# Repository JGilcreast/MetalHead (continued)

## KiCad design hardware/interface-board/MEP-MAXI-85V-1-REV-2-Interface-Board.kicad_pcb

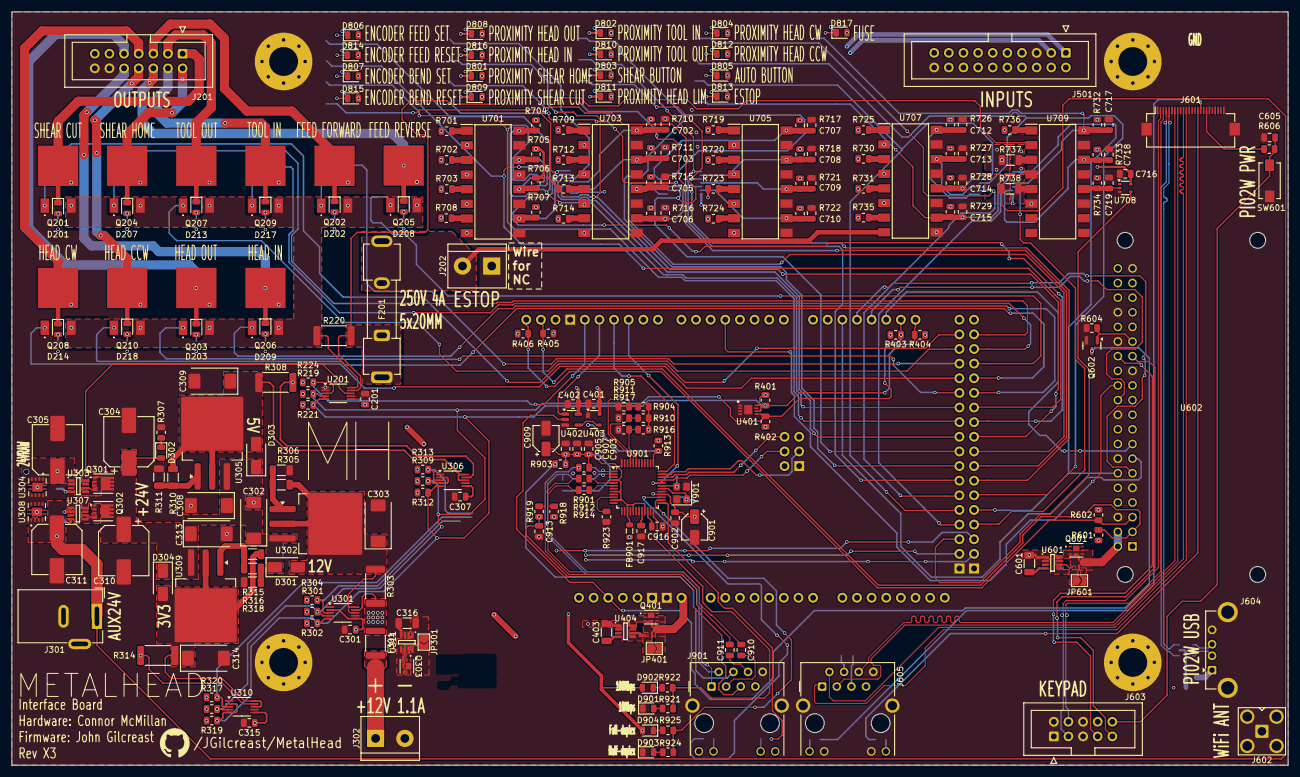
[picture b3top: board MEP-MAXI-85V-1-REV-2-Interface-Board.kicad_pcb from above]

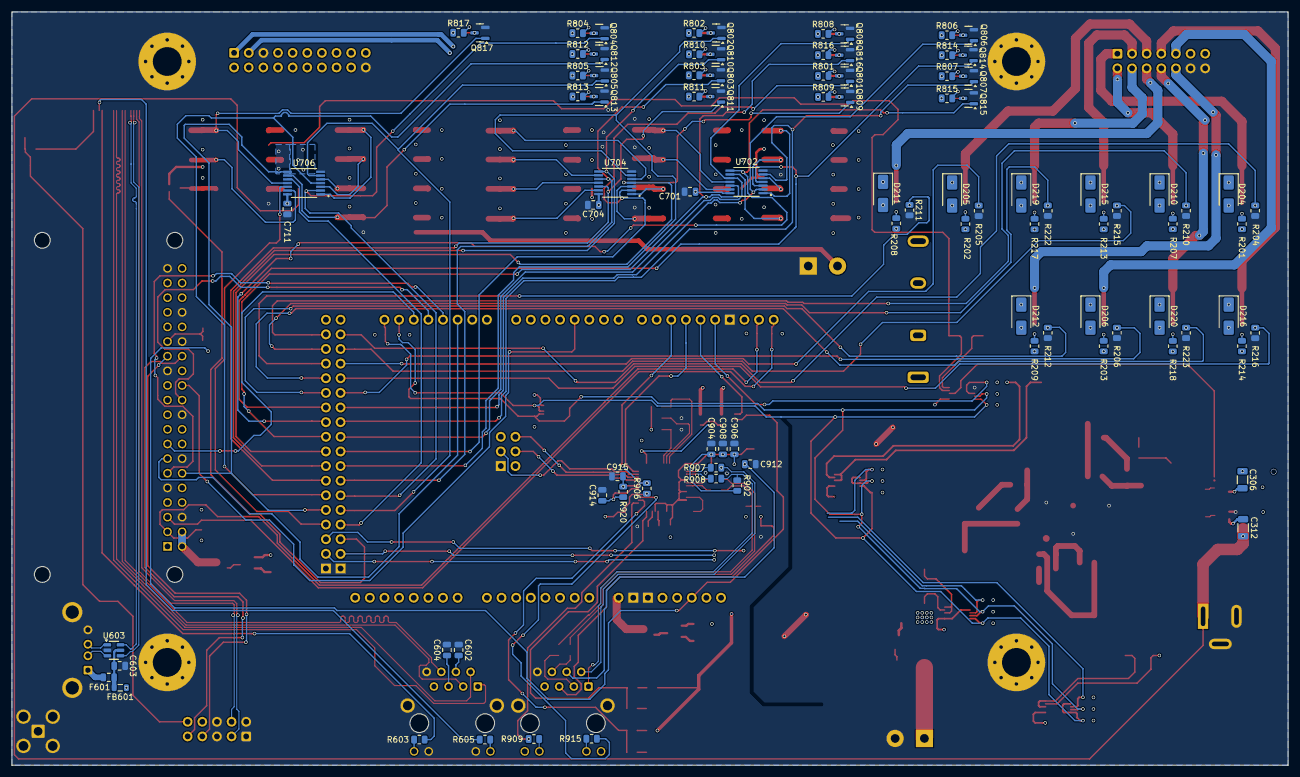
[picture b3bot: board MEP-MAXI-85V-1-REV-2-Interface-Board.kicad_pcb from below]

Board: 4 copper layers, 221.5 x 130.8 mm, 330 parts (93 on the bottom side), 244 nets.

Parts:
A401: Arduino_Due_Shield
C201, C301, C307, C315, C902, C903, C904, C905, C906, C907, C908: 0.1uF; C_0805_2012Metric
C302, C303, C308, C309, C313, C314: 10uF 50V; CP_EIA-7343-31_Kemet-D
C304, C305, C310, C311: 330uF 25V; CP_Elec_8x10.5
C306, C312, C316, C403, C601: 100nF; C_1206_3216Metric
C401, C402, C701, C702, C703, C704, C705, C706, C707, C708, C709, C710, C711, C712, C713, C714, C715, C716, C717, C718, C719: 1uF; C_0805_2012Metric
C602, C603, C604, C605: 100nF; C_0805_2012Metric
C901, C909: 10uF; CP_Elec_4x5.4
C910, C911: 6.8nF; C_0805_2012Metric
C912: 22nF; C_0805_2012Metric
C913, C916: 10nF; C_0805_2012Metric
C914, C915: 18pF; C_0805_2012Metric
C917: 4.7uF; C_0805_2012Metric
D201, D202, D203, D207, D208, D209, D213, D214, D217, D218, D901, D902, D903, D904: RED; LED_0805_2012Metric
D204, D205, D206, D210, D211, D212, D215, D216, D219, D220: SMAJ24A; D_SMA
D301, D303, D304: 1N4002 M2; D_SMA
D302, D801, D802, D803, D804, D805, D806, D807, D808, D809, D810, D811, D812, D813, D814, D815, D816, D817: BLUE; LED_0805_2012Metric
F201: 3512P; Fuseholder_Clip-5x20mm_Keystone_3512P_Inline_P23.62x7.27mm_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
F301: 16V/1.1A; Fuse_1812_4532Metric
F601: 500mA; Fuse_0805_2012Metric
FB601: 330R; L_0805_2012Metric
FB901: 120R; L_0805_2012Metric
H101, H102, H103, H104: MountingHole_Pad; MountingHole_5mm_Pad_Via
J201: Conn_02x07_Odd_Even; IDC-Header_2x07_P2.54mm_Vertical
J202, J302: Screw_Terminal_01x02; TerminalBlock_bornier-2_P5.08mm
J301: Barrel_Jack_MountingPin; BarrelJack_Wuerth_6941xx301002
J501: Conn_02x10_Odd_Even; IDC-Header_2x10_P2.54mm_Vertical
J601: Conn_01x24_MountingPin; Hirose_FH12-24S-0.5SH_1x24-1MP_P0.50mm_Horizontal
J602: Conn_Coaxial; SMA_Amphenol_901-143_Horizontal
J603: Conn_02x05_Odd_Even; IDC-Header_2x05_P2.54mm_Vertical
J604: USB_A; USB_A_Connfly_DS1095
J605, J901: RJ45_Hanrun_HR911105A_Horizontal
JP301, JP401, JP601: SolderJumper_2_Open; SolderJumper-2_P1.3mm_Open_TrianglePad1.0x1.5mm
Q201, Q202, Q203, Q204, Q205, Q206, Q207, Q208, Q209, Q210: IRFR7540TRPBF
Q301, Q302: DMT6007LFG; DMP4013LFG7
Q303, Q401, Q601: SSM6K518NU; SOT-1220UDFN6B_TOS
Q602, Q801, Q802, Q803, Q804, Q805, Q806, Q807, Q808, Q809, Q810, Q811, Q812, Q813, Q814, Q815, Q816, Q817: BSS138 JI; SOT-23
R201, R202, R203, R207, R208, R209, R213, R214, R217, R218, R801, R802, R803, R804, R805, R806, R807, R808, R809, R810, R811, R812, R813, R814, R815, R816, R817: 200R; R_0805_2012Metric
R204, R205, R206, R210, R211, R212, R215, R216, R219, R221, R222, R223, R224, R301, R302, R304, R309, R312, R313, R317, R319, R320, R401, R402, R403, R404, R604, R906, R913: 10K; R_0805_2012Metric
R220, R303, R308, R314: 2mR; R_2512_6332Metric
R305, R310, R315: 300R; R_1206_3216Metric
R306: 2K580; R_1206_3216Metric
R307: 2K2; R_0805_2012Metric
R311: 900R; R_1206_3216Metric
R316: 470R; R_1206_3216Metric
R318: 22R; R_1206_3216Metric
R405, R406, R601, R602: 4K7; R_0805_2012Metric
R603, R605, R606: 510R; R_0805_2012Metric
R701, R702, R703, R708, R709, R712, R713, R714, R719, R720, R723, R724, R725, R730, R731, R735, R736: 105R; R_0805_2012Metric
R704, R705, R706, R707, R710, R711, R715, R716, R717, R718, R721, R722, R726, R727, R728, R729, R732, R733, R734: 100K; R_0805_2012Metric
R737, R738: 1K2; R_1206_3216Metric
R901, R902: 49R9; R_0805_2012Metric
R903: 10R; R_0805_2012Metric
R904, R905, R909, R910, R911, R915, R916, R917: 330R; R_0805_2012Metric
R907, R908, R912, R914: 0R; R_0805_2012Metric
R918, R919: 82R; R_0805_2012Metric
R920: 1M; R_0805_2012Metric
R921, R922, R924, R925: 130R; R_0805_2012Metric
R923: 12.4K 1%; R_0805_2012Metric
SW601: SW_SPST_Omron_B3FS-100xP; SW_SPST_EVQPE1
U201, U301, U306, U310: INA226; VSSOP-10_3x3mm_P0.5mm
U302, U305, U309: LM1084-ADJ; TO-263-3_TabPin2
U303, U307, U311, U404, U601: LM74700QDDFRQ1; SOT65P280X110-8N
U304, U308: TVS2701DRBR; IC_TVS2701DRBR
U401: AT24C256C-MAHL-E; SON50P300X200X60-9L
U402: NC7SZ08M5X; SOT-23-5
U403: APX811-31UG-7; SOT-143
U602: RASPBERRY_PI_ZERO_2_W; MODULE_RASPBERRY_PI_ZERO_2_W
U603: USBLC6-2SC6; SOT-23-6
U701, U703, U705, U707, U709: LTV-846S; LTV846S
U702, U704, U706: SN74HC14PWR; SOP65P640X120-14N
U708: 74LVC1G14GW-Q100,1; SOT-353_SC-70-5
U901: W5500; LQFP-48_7x7mm_P0.5mm
Y901: 25MHz; Crystal_SMD_3225-4Pin_3.2x2.5mm

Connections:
24VRAW: C305.1, C306.1, J201.11, J501.6, Q301.1 (S), R737.1, U303.1 (EN), U303.5 (ANODE), U304.1 (IN), U304.2 (IN), U304.3 (IN), U304.4 (IN)
+3V3: C201.2, C301.2, C307.2, C315.2, C401.2, C402.2, C701.2, C704.2, C711.2, C716.1, C901.1, C902.1, D902.2 (A), D904.2 (A), FB901.1, J901.9, J901.12, R219.2, R221.1, R224.1, R301.2, R302.1, R304.1, R309.2, R312.1, R313.1, R314.2, R317.2, R319.1, R320.1, R401.1, R402.2, R403.2, R404.1, R405.2, R406.1, R601.2, R602.1, R701.1, R702.1, R703.1, R704.1, R705.1, R706.1, R707.1, R708.1, R709.1, R710.1, R711.1, R712.1, R713.1, R714.1, R715.1, R716.1, R717.1, R718.1, R719.1, R720.1, R721.1, R722.1, R723.1, R724.1, R725.1, R726.1, R727.1, R728.1, R729.1, R730.1, R731.1, R732.1, R733.1, R734.1, R735.1, R736.1, R904.2, R906.2, R910.2, R913.2, R916.2, U201.6 (VS), U301.2 (A0), U301.6 (VS), U306.6 (VS), U310.6 (VS), U310.9 (Vin-), U401.8 (VCC), U402.5 (VCC), U403.4 (VCC), U702.14 (VCC), U704.14 (VCC), U706.14 (VCC), U708.5 (VCC), U901.28 (VDD)
+3V3A: C903.1, C904.1, C905.1, C906.1, C907.1, C908.1, C909.1, FB901.2, R901.2, R902.2, R903.2, U901.4 (AVDD), U901.8 (AVDD), U901.11 (AVDD), U901.15 (AVDD), U901.17 (AVDD), U901.21 (AVDD)
+5V: C601.1, JP601.1 (A), Q601.1 (D), R201.1, R202.1, R203.1, R207.1, R208.1, R209.1, R213.1, R214.1, R217.1, R218.1, R308.2, R801.2, R802.2, R803.2, R804.2, R805.2, R806.2, R807.2, R808.2, R809.2, R810.2, R811.2, R812.2, R813.2, R814.2, R815.2, R816.2, R817.2, U306.9 (Vin-), U601.1 (EN), U601.5 (ANODE)
+12V: C316.1, C403.1, JP301.1 (A), JP401.1 (A), Q303.3 (S), Q401.1 (D), R303.2, U301.9 (Vin-), U311.1 (EN), U311.5 (ANODE), U404.1 (EN), U404.5 (ANODE)
+24V: C302.1, C304.1, C308.1, C310.1, C313.1, D301.1 (K), D302.2 (A), D303.1 (K), D304.1 (K), Q301.3 (D), Q302.3 (D), U201.8 (Vbus), U302.3 (VI), U303.8 (CATHODE), U305.3 (VI), U307.8 (CATHODE), U309.3 (VI)
/Arduino Due/D4_CS1/PIN4: A401.D4 (D4_CS1), U602.24 (GPIO8/SPI_~CE0)
/Arduino Due/D10/PIN10: A401.D10 (D10_CS0), R906.1, U901.32 (~SCS)
/Arduino Due/D11/PIN11: A401.D11, U901.36 (~INT)
/Arduino Due/D12/PIN12: A401.D12, U402.1
/Arduino Due/D13/PIN13: A401.D13, R224.2, U201.3 (~Alert)
/Arduino Due/D22/PIN22: A401.D22, Q201.1 (G), R204.2
/Arduino Due/D23/PIN23: A401.D23, Q204.1 (G), R210.2
/Arduino Due/D24/PIN24: A401.D24, Q207.1 (G), R215.2
/Arduino Due/D25/PIN25: A401.D25, Q209.1 (G), R222.2
/Arduino Due/D26/PIN26: A401.D26, Q202.1 (G), R205.2
/Arduino Due/D27/PIN27: A401.D27, Q205.1 (G), R211.2
/Arduino Due/D28/PIN28: A401.D28, Q208.1 (G), R216.2
/Arduino Due/D29/PIN29: A401.D29, Q210.1 (G), R223.2
/Arduino Due/D30/PIN30: A401.D30, Q203.1 (G), R206.2
/Arduino Due/D31/PIN31: A401.D31, Q206.1 (G), R212.2
/Arduino Due/D32/PIN32: A401.D32, Q806.1 (G), U702.2 (1Y)
/Arduino Due/D33/PIN33: A401.D33, Q814.1 (G), U702.4 (2Y)
/Arduino Due/D34/PIN34: A401.D34, Q807.1 (G), U702.6 (3Y)
/Arduino Due/D35/PIN35: A401.D35, Q815.1 (G), U702.8 (4Y)
/Arduino Due/D36/PIN36: A401.D36, Q808.1 (G), U702.10 (5Y)
/Arduino Due/D37/PIN37: A401.D37, Q816.1 (G), U702.12 (6Y)
/Arduino Due/D38/PIN38: A401.D38, Q801.1 (G), U704.2 (1Y)
/Arduino Due/D39/PIN39: A401.D39, Q809.1 (G), U704.4 (2Y)
/Arduino Due/D40/PIN40: A401.D40, Q802.1 (G), U704.6 (3Y)
/Arduino Due/D41/PIN41: A401.D41, Q810.1 (G), U704.8 (4Y)
/Arduino Due/D42/PIN42: A401.D42, Q803.1 (G), U704.10 (5Y)
/Arduino Due/D43/PIN43: A401.D43, Q811.1 (G), U704.12 (6Y)
/Arduino Due/D44/PIN44: A401.D44, Q804.1 (G), U706.2 (1Y)
/Arduino Due/D45/PIN45: A401.D45, Q812.1 (G), U706.4 (2Y)
/Arduino Due/D46/PIN46: A401.D46, Q805.1 (G), U706.6 (3Y)
/Arduino Due/D47/PIN47: A401.D47, U602.12 (GPIO18/GPIO_GEN1), U706.8 (4Y)
/Arduino Due/D48/PIN48: A401.D48, U706.10 (5Y)
/Arduino Due/D49/PIN49: A401.D49, U706.12 (6Y)
/Arduino Due/D50/PIN50: A401.D50, U708.4
/Arduino Due/D51/PIN51: A401.D51, R304.2, U301.3 (~Alert)
/Arduino Due/D52/PIN52: A401.D52 (D52_CS2), R313.2, U306.3 (~Alert)
/Arduino Due/D53/PIN53: A401.D53, R320.2, U310.3 (~Alert)
/Arduino Due/HMI_I2C_SCL1: A401.SCL1, R406.2, R602.2, U602.5 (GPIO3/SCL)
/Arduino Due/HMI_I2C_SDA1: A401.SDA1, R405.1, R601.1, U602.3 (GPIO2/SDA1)
/Arduino Due/HMI_UART_RX1: A401.D19 (D19/RX1), U602.15 (GPIO22/GPIO_GEN3)
/Arduino Due/HMI_UART_RX2: A401.D17 (D17/RX2), U602.11 (GPIO17/GPIO_GEN0)
/Arduino Due/HMI_UART_TX1: A401.D18 (D18/TX1), U602.22 (GPIO25/GPIO_GEN6)
/Arduino Due/HMI_UART_TX2: A401.D16 (D16/TX2), U602.13 (GPIO27/GPIO_GEN2)
/Arduino Due/SPI_MISO: A401.MISO (SPI_MISO), U602.21 (GPIO9/SPI_MISO), U901.34 (MISO)
/Arduino Due/SPI_MOSI: A401.MOSI (SPI_MOSI), U602.19 (GPIO10/SPI_MOSI), U901.35 (MOSI)
/Arduino Due/SPI_SCK: A401.SCK (SPI_SCK), U602.23 (GPIO11/SPI_SCLK), U901.33 (SCLK)
/Arduino Due/VIN: A401.VIN, JP401.2 (B), Q401.3 (S), U404.8 (CATHODE)
/Arduino Due/~ATSAM3X8E_RESET: A401.RST1 (RESET), Q602.3 (D), U402.2
/Arduino Due/~W5500_RST: R913.1, U403.2 (~RESET), U901.37 (~RST)
/External Power/3V3OUT: C314.1, D304.2 (A), R314.1, R315.1, U309.2 (VO), U310.8 (Vbus), U310.10 (Vin+)
/External Power/5VOUT: C309.1, D303.2 (A), R308.1, R310.1, U305.2 (VO), U306.8 (Vbus), U306.10 (Vin+)
/External Power/12V: F301.1, JP301.2 (B), Q303.1 (D), U311.8 (CATHODE)
/External Power/12VOUT: C303.1, D301.2 (A), R303.1, R305.1, U301.8 (Vbus), U301.10 (Vin+), U302.2 (VO)
/External Power/+12V-HMI-FUSED: F301.2, J302.1
/Input Connections/AUTO_BUTTON: J501.17, U707.6 (C3)
/Input Connections/ENCODER_BEND_RESET: J501.4, U701.8 (C4)
/Input Connections/ENCODER_BEND_SET: J501.3, U701.6 (C3)
/Input Connections/ENCODER_FEED_RESET: J501.2, U701.4 (C2)
/Input Connections/ENCODER_FEED_SET: J501.1, U701.2 (C1)
/Input Connections/PROXIMITY_HEAD_CCW: J501.16, U707.4 (C2)
/Input Connections/PROXIMITY_HEAD_CW: J501.15, U707.2 (C1)
/Input Connections/PROXIMITY_HEAD_IN: J501.8, U703.4 (C2)
/Input Connections/PROXIMITY_HEAD_LIM: J501.14, U705.8 (C4)
/Input Connections/PROXIMITY_HEAD_OUT: J501.7, U703.2 (C1)
/Input Connections/PROXIMITY_SHEAR_CUT: J501.10, U703.8 (C4)
/Input Connections/PROXIMITY_SHEAR_HOME: J501.9, U703.6 (C3)
/Input Connections/PROXIMITY_TOOL_IN: J501.11, U705.2 (C1)
/Input Connections/PROXIMITY_TOOL_OUT: J501.12, U705.4 (C2)
/Input Connections/SHEAR_BUTTON: J501.13, U705.6 (C3)
/Output Connections/ESTOP: F201.2, J202.2, U707.8 (C4)
/Output Connections/FUSE: F201.1, R220.2, U201.9 (Vin-), U709.2 (C1)
/Output Connections/FUSED_GND: D204.2 (A2), D205.2 (A2), D206.2 (A2), D210.2 (A2), D211.2 (A2), D212.2 (A2), D215.2 (A2), D216.2 (A2), D219.2 (A2), D220.2 (A2), Q201.3 (S), Q202.3 (S), Q203.3 (S), Q204.3 (S), Q205.3 (S), Q206.3 (S), Q207.3 (S), Q208.3 (S), Q209.3 (S), Q210.3 (S), R220.1, U201.10 (Vin+)
/Output Connections/SOL_FEED_FORWARD: D202.1 (K), D205.1 (A1), J201.5, Q202.2 (D)
/Output Connections/SOL_FEED_REVERSE: D208.1 (K), D211.1 (A1), J201.6, Q205.2 (D)
/Output Connections/SOL_HEAD_CCW: D218.1 (K), D220.1 (A1), J201.8, Q210.2 (D)
/Output Connections/SOL_HEAD_CW: D214.1 (K), D216.1 (A1), J201.7, Q208.2 (D)
/Output Connections/SOL_HEAD_IN: D209.1 (K), D212.1 (A1), J201.10, Q206.2 (D)
/Output Connections/SOL_HEAD_OUT: D203.1 (K), D206.1 (A1), J201.9, Q203.2 (D)
/Output Connections/SOL_SHEER_CUT: D201.1 (K), D204.1 (A1), J201.1, Q201.2 (D)
/Output Connections/SOL_SHEER_HOME: D207.1 (K), D210.1 (A1), J201.2, Q204.2 (D)
/Output Connections/SOL_TOOL_IN: D217.1 (K), D219.1 (A1), J201.4, Q209.2 (D)
/Output Connections/SOL_TOOL_OUT: D213.1 (K), D215.1 (A1), J201.3, Q207.2 (D)
/Pi Zero 2W SBC/5V: FB601.2, J603.8, JP601.2 (B), Q601.3 (S), U601.8 (CATHODE), U602.2 (5V_2), U602.4 (5V_4)
/Pi Zero 2W SBC/D+: J604.3 (D+), U603.1 (I/O1)
/Pi Zero 2W SBC/D-: J604.2 (D-), U603.3 (I/O2)
/Pi Zero 2W SBC/EPHY-RXN: J601.7, J605.6 (RD-)
/Pi Zero 2W SBC/EPHY-RXP: J601.8, J605.3 (RD+)
/Pi Zero 2W SBC/EPHY-TXN: J601.10, J605.2 (TD-)
/Pi Zero 2W SBC/EPHY-TXP: J601.11, J605.1 (TD+)
/Pi Zero 2W SBC/PC15: J601.15, R603.2
/Pi Zero 2W SBC/PC16: J601.16, R605.2
/Pi Zero 2W SBC/PI0/ATSAM3X8E-RESET: Q602.1 (G), R604.1, U602.29 (GPIO5)
/Pi Zero 2W SBC/PWRON: J601.18, R606.1
/Pi Zero 2W SBC/PWRSW: C605.1, J603.10, R606.2, SW601.1
/Pi Zero 2W SBC/TWI2_SCL/UART3_TX: J603.9, U602.28 (ID_SC)
/Pi Zero 2W SBC/TWI2_SDA/UART3_RX: J603.7, U602.27 (ID_SD)
/Pi Zero 2W SBC/USB2-D+: J601.5, U603.6 (I/O1)
/Pi Zero 2W SBC/USB2-D-: J601.4, U603.4 (I/O2)
/Pi Zero 2W SBC/USB3-D+: J601.3, J603.4
/Pi Zero 2W SBC/USB3-D-: J601.2, J603.3
/Signal Processing/24VRAW*: C718.1, R733.2, U706.13 (6A), U709.14 (C2)
/Signal Processing/AUTO_BUTTON*: C714.1, R728.2, U706.5 (3A), U707.12 (C3)
/Signal Processing/AUX24V*: C719.1, R734.2, U708.2, U709.12 (C3)
/Signal Processing/ENCODER_BEND_RESET*: R707.2, U701.10 (C4), U702.9 (4A)
/Signal Processing/ENCODER_BEND_SET*: R706.2, U701.12 (C3), U702.5 (3A)
/Signal Processing/ENCODER_FEED_RESET*: R705.2, U701.14 (C2), U702.3 (2A)
/Signal Processing/ENCODER_FEED_SET*: R704.2, U701.16 (C1), U702.1 (1A)
/Signal Processing/ESTOP*: C715.1, Q813.1 (G), R729.2, U706.9 (4A), U707.10 (C4)
/Signal Processing/FUSE*: C717.1, Q817.1 (G), R732.2, U706.11 (5A), U709.16 (C1)
/Signal Processing/PROXIMITY_HEAD_CCW*: C713.1, R727.2, U706.3 (2A), U707.14 (C2)
/Signal Processing/PROXIMITY_HEAD_CW*: C712.1, R726.2, U706.1 (1A), U707.16 (C1)
/Signal Processing/PROXIMITY_HEAD_IN*: C703.1, R711.2, U702.13 (6A), U703.14 (C2)
/Signal Processing/PROXIMITY_HEAD_LIM*: C710.1, R722.2, U704.13 (6A), U705.10 (C4)
/Signal Processing/PROXIMITY_HEAD_OUT*: C702.1, R710.2, U702.11 (5A), U703.16 (C1)
/Signal Processing/PROXIMITY_SHEAR_CUT*: C706.1, R716.2, U703.10 (C4), U704.3 (2A)
/Signal Processing/PROXIMITY_SHEAR_HOME*: C705.1, R715.2, U703.12 (C3), U704.1 (1A)
/Signal Processing/PROXIMITY_TOOL_IN*: C707.1, R717.2, U704.5 (3A), U705.16 (C1)
/Signal Processing/PROXIMITY_TOOL_OUT*: C708.1, R718.2, U704.9 (4A), U705.14 (C2)
/Signal Processing/SHEAR_BUTTON*: C709.1, R721.2, U704.11 (5A), U705.12 (C3)
/WIZnet W5500 ENET PHY/1V2O: C916.1, U901.22 (1V2O)
/WIZnet W5500 ENET PHY/ACTLED: R915.1, U901.27 (ACTLED)
/WIZnet W5500 ENET PHY/DUPLED: R924.1, R925.2, U901.26 (DUPLED)
/WIZnet W5500 ENET PHY/EXRES1: R923.2, U901.10 (EXRES1)
/WIZnet W5500 ENET PHY/LINKLED: R909.1, U901.25 (LINKLED)
/WIZnet W5500 ENET PHY/PMODE0: R904.1, R905.2, U901.45 (PMODE0)
/WIZnet W5500 ENET PHY/PMODE1: R910.1, R911.2, U901.44 (PMODE1)
/WIZnet W5500 ENET PHY/PMODE2: R916.1, R917.2, U901.43 (PMODE2)
/WIZnet W5500 ENET PHY/RCT: C913.1, J901.5 (RCT), R918.1, R919.1
/WIZnet W5500 ENET PHY/RD+: C910.2, J901.3 (RD+)
/WIZnet W5500 ENET PHY/RD-: C911.2, J901.6 (RD-)
/WIZnet W5500 ENET PHY/RX+: C910.1, R914.2, R918.2
/WIZnet W5500 ENET PHY/RX-: C911.1, R912.2, R919.2
/WIZnet W5500 ENET PHY/RXN: R912.1, U901.5 (RXN)
/WIZnet W5500 ENET PHY/RXP: R914.1, U901.6 (RXP)
/WIZnet W5500 ENET PHY/SPDLED: R921.1, R922.2, U901.24 (SPDLED)
/WIZnet W5500 ENET PHY/TD+: J901.1 (TD+), R902.1, R908.2
/WIZnet W5500 ENET PHY/TD-: J901.2 (TD-), R901.1, R907.2
/WIZnet W5500 ENET PHY/TOCAP: C917.1, U901.20 (TOCAP)
/WIZnet W5500 ENET PHY/TXN: R907.1, U901.1 (TXN)
/WIZnet W5500 ENET PHY/TXP: R908.1, U901.2 (TXP)
/WIZnet W5500 ENET PHY/XI: C914.1, R920.1, U901.30 (XI/CLKIN), Y901.1
/WIZnet W5500 ENET PHY/XO: C915.1, R920.2, U901.31 (XO), Y901.3
AUX24V: C311.1, C312.1, J301.1, Q302.1 (S), R738.1, U307.1 (EN), U307.5 (ANODE), U308.1 (IN), U308.2 (IN), U308.3 (IN), U308.4 (IN)
GND: A401.GND1 (GND), A401.GND2 (GND), A401.GND3 (GND), A401.GND4 (SPI_GND), A401.GND5 (GND), A401.GND6 (GND), C201.1, C301.1, C302.2, C303.2, C304.2, C305.2, C307.1, C308.2, C309.2, C310.2, C311.2, C313.2, C314.2, C315.1, C401.1, C402.1, C602.2, C603.1, C604.2, C605.2, C701.1, C702.2, C703.2, C704.1, C705.2, C706.2, C707.2, C708.2, C709.2, C710.2, C711.1, C712.2, C713.2, C714.2, C715.2, C716.2, C717.2, C718.2, C719.2, C901.2, C902.2, C903.2, C904.2, C905.2, C906.2, C907.2, C908.2, C909.2, C912.2, C913.2, C914.2, C915.2, C916.2, C917.2, D901.1 (K), D903.1 (K), H101.1, H102.1, H103.1, H104.1, J201.12, J201.14, J202.1, J301.2, J301.3 (MountPin), J302.2, J501.5, J501.20, J601.1, J601.6, J601.12, J601.19, J601.21, J601.24, J601.MP (MountPin), J602.1 (In), J602.2 (Ext), J603.1, J603.2, J603.5, J603.6, J604.4 (GND), J604.5 (Shield), J605.8, J605.10, J605.11, J605.SH, J901.8, J901.SH, Q602.2 (S), Q801.2 (S), Q802.2 (S), Q803.2 (S), Q804.2 (S), Q805.2 (S), Q806.2 (S), Q807.2 (S), Q808.2 (S), Q809.2 (S), Q810.2 (S), Q811.2 (S), Q812.2 (S), Q813.2 (S), Q814.2 (S), Q815.2 (S), Q816.2 (S), Q817.2 (S), R204.1, R205.1, R206.1, R210.1, R211.1, R212.1, R215.1, R216.1, R222.1, R223.1, R306.2, R307.1, R311.2, R318.2, R604.2, R905.1, R911.1, R917.1, R923.1, SW601.2, U201.1 (A1), U201.2 (A0), U201.7 (GND), U301.1 (A1), U301.7 (GND), U303.2 (GND), U304.5 (GND), U304.6 (GND), U304.7 (GND), U304.8 (GND), U306.1 (A1), U306.7 (GND), U307.2 (GND), U308.5 (GND), U308.6 (GND), U308.7 (GND), U308.8 (GND), U310.1 (A1), U310.7 (GND), U311.2 (GND), U401.1 (A0), U401.2 (A1), U401.3 (A2), U401.4 (GND), U401.7 (WP), U401.9 (EP), U402.3 (GND), U403.1 (GND), U404.2 (GND), U601.2 (GND), U602.6 (GND_6), U602.9 (GND_9), U602.14 (GND_14), U602.20 (GND_20), U602.25 (GND_25), U602.30 (GND_30), U602.34 (GND_34), U602.39 (GND_39), U603.2 (GND), U701.9 (E4), U701.11 (E3), U701.13 (E2), U701.15 (E1), U702.7 (GND), U703.9 (E4), U703.11 (E3), U703.13 (E2), U703.15 (E1), U704.7 (GND), U705.9 (E4), U705.11 (E3), U705.13 (E2), U705.15 (E1), U706.7 (GND), U707.9 (E4), U707.11 (E3), U707.13 (E2), U707.15 (E1), U708.3 (GND), U709.4 (C2), U709.6 (C3), U709.11 (E3), U709.13 (E2), U709.15 (E1), U901.3 (AGND), U901.9 (AGND), U901.14 (AGND), U901.16 (AGND), U901.19 (AGND), U901.29 (GND), U901.48 (AGND), Y901.2, Y901.4
unnamed: D201.2 (A), R201.2
unnamed: D202.2 (A), R202.2
unnamed: D203.2 (A), R203.2
unnamed: D207.2 (A), R207.2
unnamed: D208.2 (A), R208.2
unnamed: D209.2 (A), R209.2
unnamed: D213.2 (A), R213.2
unnamed: D214.2 (A), R214.2
unnamed: D217.2 (A), R217.2
unnamed: D218.2 (A), R218.2
unnamed: D302.1 (K), R307.2
unnamed: D801.2 (A), R801.1
unnamed: D801.1 (K), Q801.3 (D)
unnamed: D802.2 (A), R802.1
unnamed: D802.1 (K), Q802.3 (D)
unnamed: D803.2 (A), R803.1
unnamed: D803.1 (K), Q803.3 (D)
unnamed: D804.2 (A), R804.1
unnamed: D804.1 (K), Q804.3 (D)
unnamed: D805.2 (A), R805.1
unnamed: D805.1 (K), Q805.3 (D)
unnamed: D806.2 (A), R806.1
unnamed: D806.1 (K), Q806.3 (D)
unnamed: D807.2 (A), R807.1
unnamed: D807.1 (K), Q807.3 (D)
unnamed: D808.2 (A), R808.1
unnamed: D808.1 (K), Q808.3 (D)
unnamed: D809.2 (A), R809.1
unnamed: D809.1 (K), Q809.3 (D)
unnamed: D810.2 (A), R810.1
unnamed: D810.1 (K), Q810.3 (D)
unnamed: D811.2 (A), R811.1
unnamed: D811.1 (K), Q811.3 (D)
unnamed: D812.2 (A), R812.1
unnamed: D812.1 (K), Q812.3 (D)
unnamed: D813.2 (A), R813.1
unnamed: D813.1 (K), Q813.3 (D)
unnamed: D814.2 (A), R814.1
unnamed: D814.1 (K), Q814.3 (D)
unnamed: D815.2 (A), R815.1
unnamed: D815.1 (K), Q815.3 (D)
unnamed: D816.2 (A), R816.1
unnamed: D816.1 (K), Q816.3 (D)
unnamed: D817.2 (A), R817.1
unnamed: D817.1 (K), Q817.3 (D)
unnamed: D901.2 (A), R921.2
unnamed: D902.1 (K), R922.1
unnamed: D903.2 (A), R924.2
unnamed: D904.1 (K), R925.1
unnamed: F601.1, J604.1 (VBUS)
unnamed: J605.9, R605.1
unnamed: J605.12, R603.1
unnamed: C604.1, J605.5 (RCT)
unnamed: C602.1, J605.4 (TCT)
unnamed: J901.10, R915.2
unnamed: J901.11, R909.2
unnamed: C912.1, J901.4 (TCT), R903.1
unnamed: Q301.2 (G), U303.6 (GATE)
unnamed: Q302.2 (G), U307.6 (GATE)
unnamed: Q303.2 (G), U311.6 (GATE)
unnamed: Q401.2 (G), U404.6 (GATE)
unnamed: Q601.2 (G), U601.6 (GATE)
unnamed: R316.2, R318.1
unnamed: R305.2, R306.1, U302.1 (ADJ)
unnamed: C306.2, U303.4 (VCAP)
unnamed: R310.2, R311.1, U305.1 (ADJ)
unnamed: C312.2, U307.4 (VCAP)
unnamed: R315.2, R316.1, U309.1 (ADJ)
unnamed: C316.2, U311.4 (VCAP)
unnamed: U402.4, U403.3 (~MR)
unnamed: C403.2, U404.4 (VCAP)
unnamed: C601.2, U601.4 (VCAP)
unnamed: C603.2, F601.2, FB601.1, U603.5 (VBUS)
unnamed: R701.2, U701.1 (A1)
unnamed: R702.2, U701.3 (A2)
unnamed: R703.2, U701.5 (A3)
unnamed: R708.2, U701.7 (A4)
unnamed: R709.2, U703.1 (A1)
unnamed: R712.2, U703.3 (A2)
unnamed: R713.2, U703.5 (A3)
unnamed: R714.2, U703.7 (A4)
unnamed: R719.2, U705.1 (A1)
unnamed: R720.2, U705.3 (A2)
unnamed: R723.2, U705.5 (A3)
unnamed: R724.2, U705.7 (A4)
unnamed: R725.2, U707.1 (A1)
unnamed: R730.2, U707.3 (A2)
unnamed: R731.2, U707.5 (A3)
unnamed: R735.2, U707.7 (A4)
unnamed: R736.2, U709.1 (A1)
unnamed: R737.2, U709.3 (A2)
unnamed: R738.2, U709.5 (A3)
SCL: A401.D21 (D21/SCL), R221.2, R302.2, R312.2, R319.2, R401.2, R404.2, U201.5 (SCL), U301.5 (SCL), U306.5 (SCL), U310.2 (A0), U310.5 (SCL), U401.6 (SCL)
SDA: A401.D20 (D20/SDA), R219.1, R301.1, R309.1, R317.1, R402.1, R403.1, U201.4 (SDA), U301.4 (SDA), U306.2 (A0), U306.4 (SDA), U310.4 (SDA), U401.5 (SDA)
